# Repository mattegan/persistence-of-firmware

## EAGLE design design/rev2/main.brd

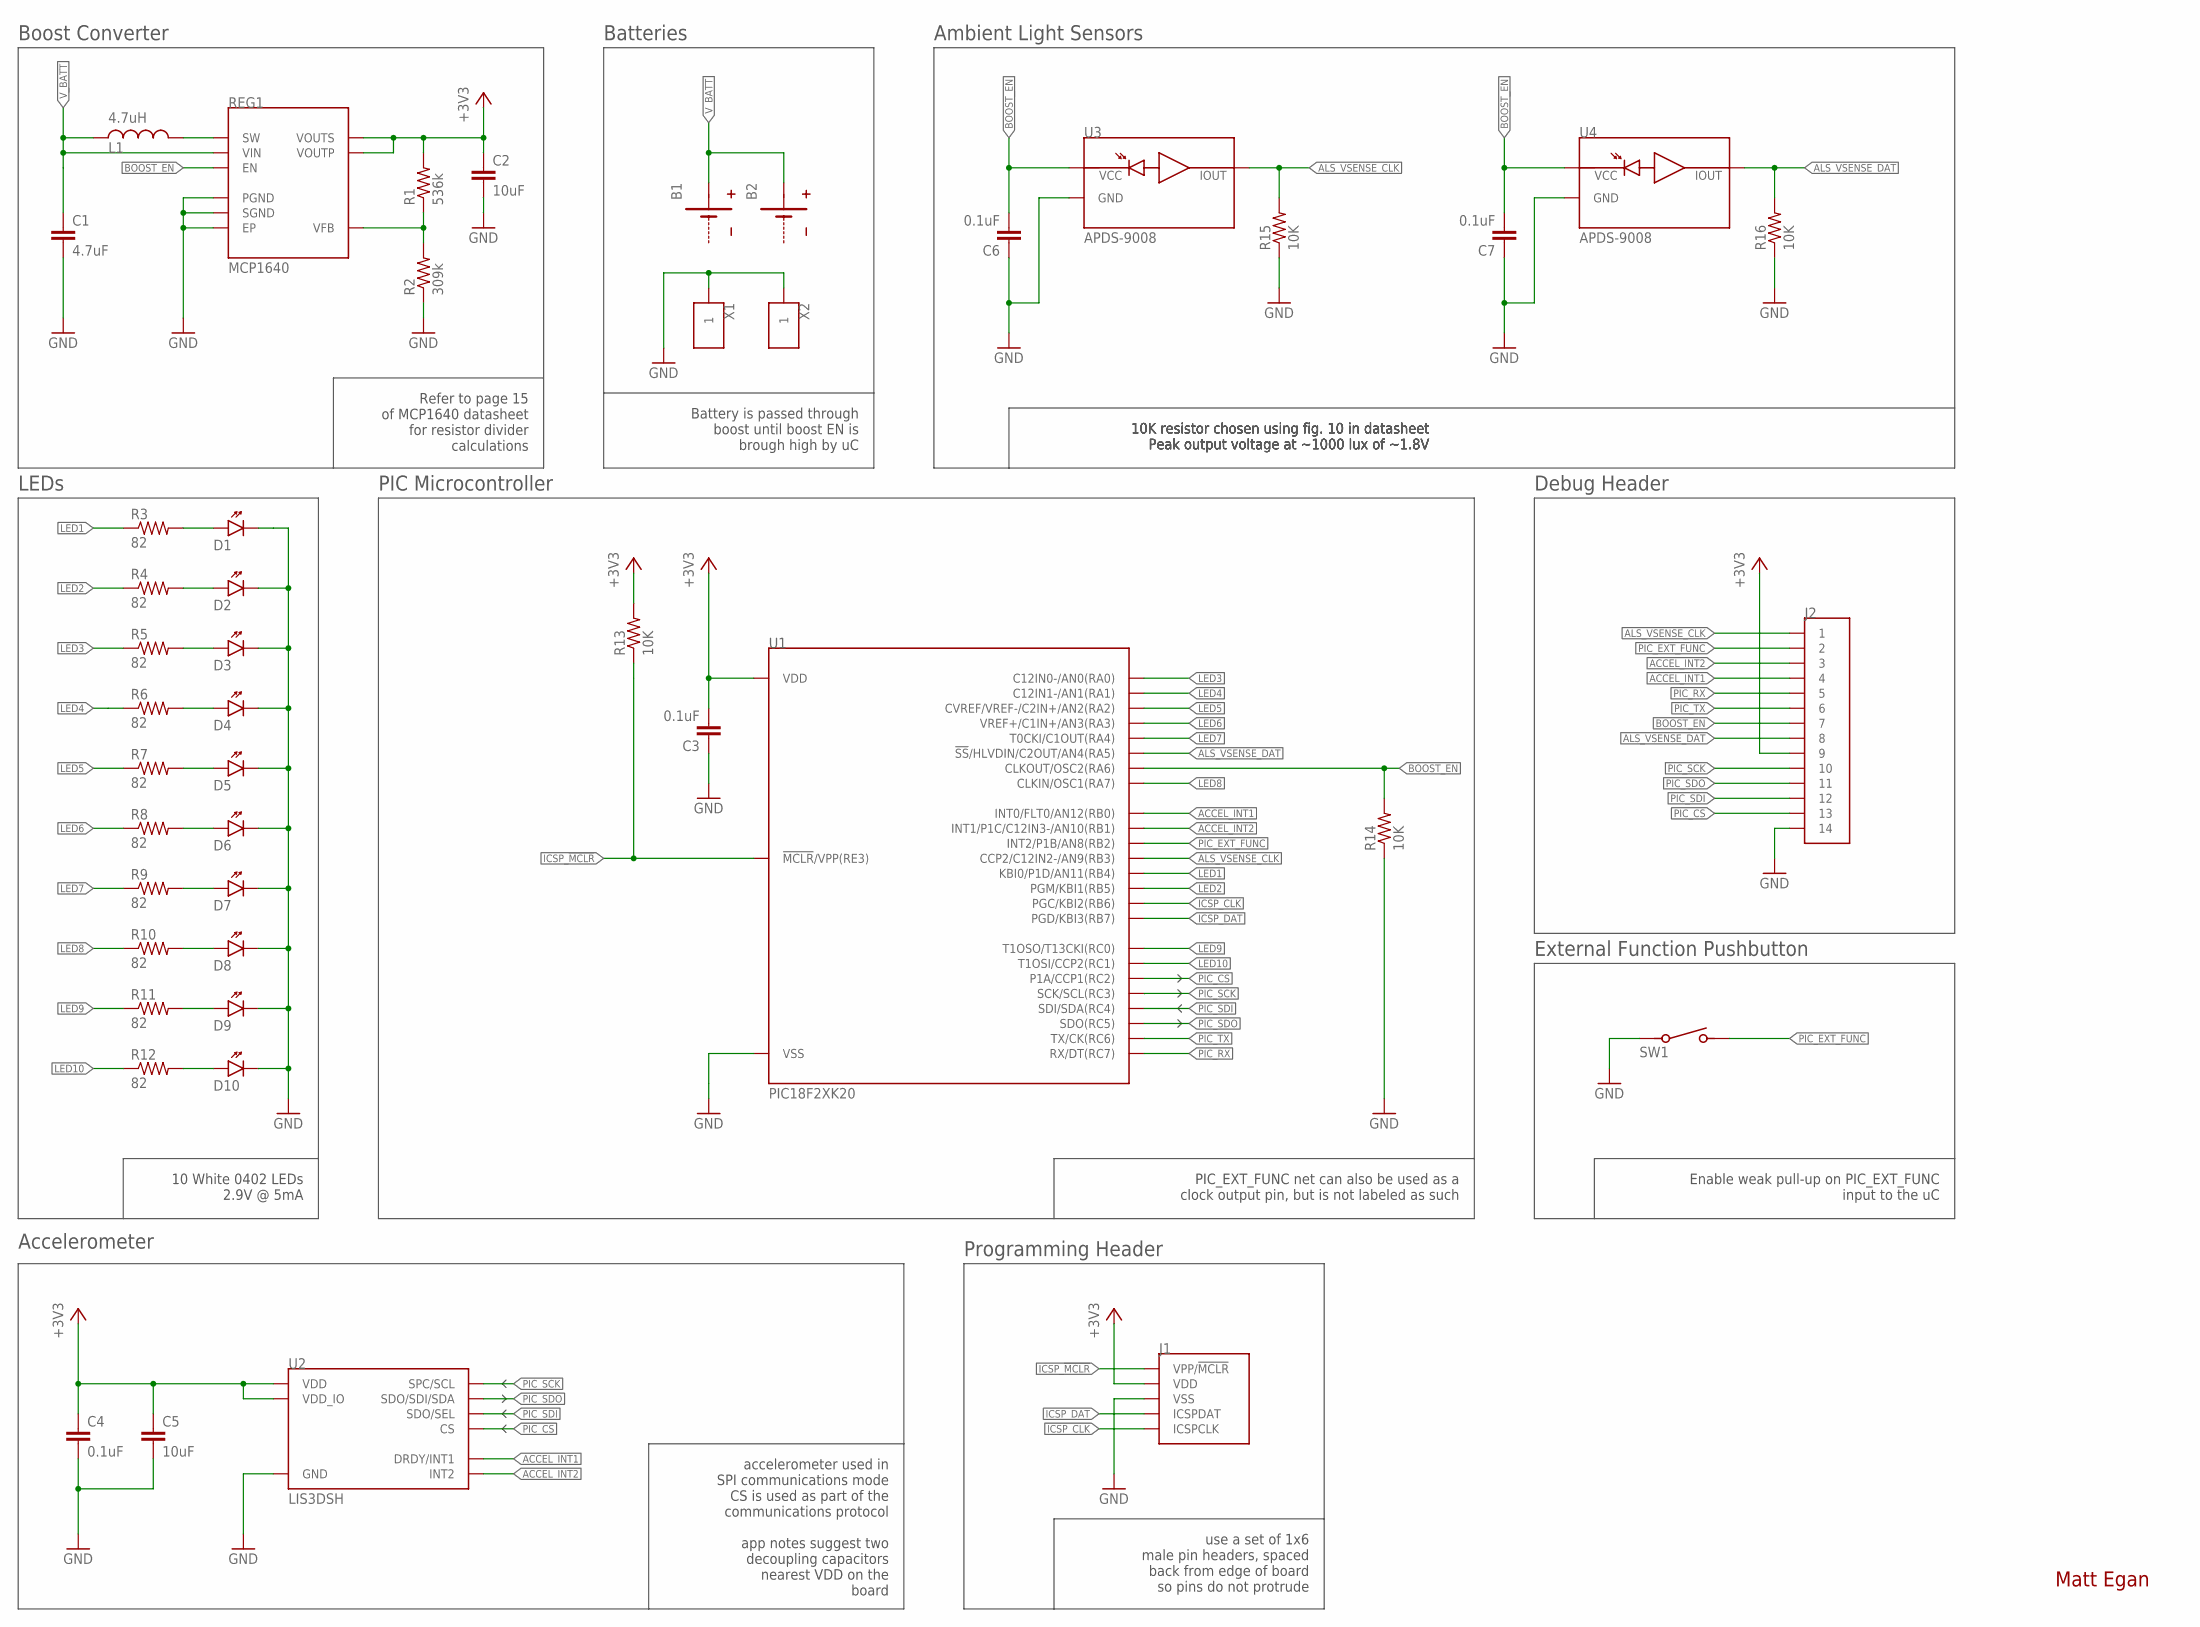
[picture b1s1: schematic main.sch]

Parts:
B1, B2: BATTERY-POS-HALF; CR20XX-PLATED
C1: 4.7uF; SMD-0603
C2: 10uF; SMD-0603
C3, C4, C6, C7: 0.1uF; SMD-0805
C5: 10uF; SMD-0805
D1, D2, D3, D4, D5, D6, D7, D8, D9, D10: LED0603; SMD-0603-P
J1: ICSP-HEADER1X6-0.1-ICSP-PADS; 1X6-0.1-ICSP-PADS
J2: HEADER-141X14-0.05-PADS; 1X14-0.05-PADS
L1: 4.7uH; VLF403210MT
R1: 536k; SMD-0603
R2: 309k; SMD-0603
R3, R4, R5, R6, R7, R8, R9, R10, R11, R12: 82; SMD-0603
R13, R14, R15, R16: 10K; SMD-0603
REG1: MCP1640; DFN-8(2X3)
SW1: B3U-3000P
U1: PIC18F2XK20; QFN-28
U2: LIS3DSH; LGA-16
U3, U4: APDS-9008; AVAGO-CHIPLED6
X1, X2: TE-2199248-X

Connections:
+3V3: C2.1, C3.2, C4.1, C5.1, J1.P$2 (VDD), J2.P$9 (9), R1.2, R13.2, REG1.6 (VOUTP), REG1.7 (VOUTS), U1.P$17 (VDD), U2.P$1 (VDD_IO), U2.P$14 (VDD), U2.P$15 (VDD)
ACCEL_INT1: J2.P$4 (4), U1.P$18 (INT0/FLT0/AN12(RB0)), U2.P$11 (DRDY/INT1)
ACCEL_INT2: J2.P$3 (3), U1.P$19 (INT1/P1C/C12IN3-/AN10(RB1)), U2.P$9 (INT2)
ALS_VSENSE_CLK: J2.P$1 (1), R15.2, U1.P$21 (CCP2/C12IN2-/AN9(RB3)), U3.P$6 (P$IOUT)
ALS_VSENSE_DAT: J2.P$8 (8), R16.2, U1.P$4 (!SS!/HLVDIN/C2OUT/AN4(RA5)), U4.P$6 (P$IOUT)
BOOST_EN: C6.2, C7.2, J2.P$7 (7), R14.2, REG1.4 (EN), U1.P$7 (CLKOUT/OSC2(RA6)), U3.P$1 (P$VCC), U4.P$1 (P$VCC)
GND: C1.2, C2.2, C3.1, C4.2, C5.2, C6.1, C7.1, D1.-, D2.-, D3.-, D4.-, D5.-, D6.-, D7.-, D8.-, D9.-, D10.-, J1.P$3 (VSS), J2.P$14 (14), R2.1, R14.1, R15.1, R16.1, REG1.2 (SGND), REG1.3 (PGND), REG1.EP, SW1.SW$1 (1), U1.P$5 (VSS), U1.P$16 (VSS), U2.P$5 (GND), U2.P$10 (GND), U2.P$12 (GND), U2.P$13 (GND), U2.P$16 (GND), U3.P$4 (GND), U4.P$4 (GND), X1.P$1, X1.P$2, X2.P$1, X2.P$2
ICSP_!MCLR!: J1.P$1 (VPP/!MCLR!), R13.1, U1.P$26 (!MCLR!/VPP(RE3))
ICSP_CLK: J1.P$5 (ICSPCLK), U1.P$24 (PGC/KBI2(RB6))
ICSP_DAT: J1.P$4 (ICSPDAT), U1.P$25 (PGD/KBI3(RB7))
LED1: R3.1, U1.P$22 (KBI0/P1D/AN11(RB4))
LED2: R4.1, U1.P$23 (PGM/KBI1(RB5))
LED3: R5.1, U1.P$27 (C12IN0-/AN0(RA0))
LED4: R6.1, U1.P$28 (C12IN1-/AN1(RA1))
LED5: R7.1, U1.P$1 (CVREF/VREF-/C2IN+/AN2(RA2))
LED6: R8.1, U1.P$2 (VREF+/C1IN+/AN3(RA3))
LED7: R9.1, U1.P$3 (T0CKI/C1OUT(RA4))
LED8: R10.1, U1.P$6 (CLKIN/OSC1(RA7))
LED9: R11.1, U1.P$8 (T1OSO/T13CKI(RC0))
LED10: R12.1, U1.P$9 (T1OSI/CCP2(RC1))
unnamed: L1.P$2 (2), REG1.5 (SW)
unnamed: R1.1, R2.2, REG1.1 (VFB)
unnamed: D1.+, R3.2
unnamed: D2.+, R4.2
unnamed: D3.+, R5.2
unnamed: D4.+, R6.2
unnamed: D5.+, R7.2
unnamed: D6.+, R8.2
unnamed: D7.+, R9.2
unnamed: D8.+, R10.2
unnamed: D9.+, R11.2
unnamed: D10.+, R12.2
PIC_CS: J2.P$13 (13), U1.P$10 (P1A/CCP1(RC2)), U2.P$8 (CS)
PIC_EXT_FUNC: J2.P$2 (2), SW1.SW$2 (3), U1.P$20 (INT2/P1B/AN8(RB2))
PIC_RX: J2.P$5 (5), U1.P$15 (RX/DT(RC7))
PIC_SCK: J2.P$10 (10), U1.P$11 (SCK/SCL(RC3)), U2.P$4 (SPC/SCL)
PIC_SDI: J2.P$12 (12), U1.P$12 (SDI/SDA(RC4)), U2.P$7 (SDO/SEL)
PIC_SDO: J2.P$11 (11), U1.P$13 (SDO(RC5)), U2.P$6 (SDO/SDI/SDA)
PIC_TX: J2.P$6 (6), U1.P$14 (TX/CK(RC6))
V_BATT: B1.P$1, B2.P$1, C1.1, L1.P$1 (1), REG1.8 (VIN)

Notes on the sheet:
Matt Egan
Accelerometer
Refer to page 15 of MCP1640 datasheet for resistor divider calculations
Boost Converter
Batteries
LEDs
10 White 0402 LEDs 2.9V @ 5mA
Programming Header
Ambient Light Sensors
10K resistor chosen using fig. 10 in datasheet Peak output voltage at ~1000 lux of ~1.8V
use a set of 1x6 male pin headers, spaced back from edge of board so pins do not protrude
Debug Header
PIC Microcontroller
accelerometer used in SPI communications mode CS is used as part of the communications protocol app notes suggest two decoupling capacitors nearest VDD on the board
External Function Pushbutton
PIC_EXT_FUNC net can also be used as a clock output pin, but is not labeled as such
Battery is passed through boost until boost EN is brough high by uC
Enable weak pull-up on PIC_EXT_FUNC input to the uC

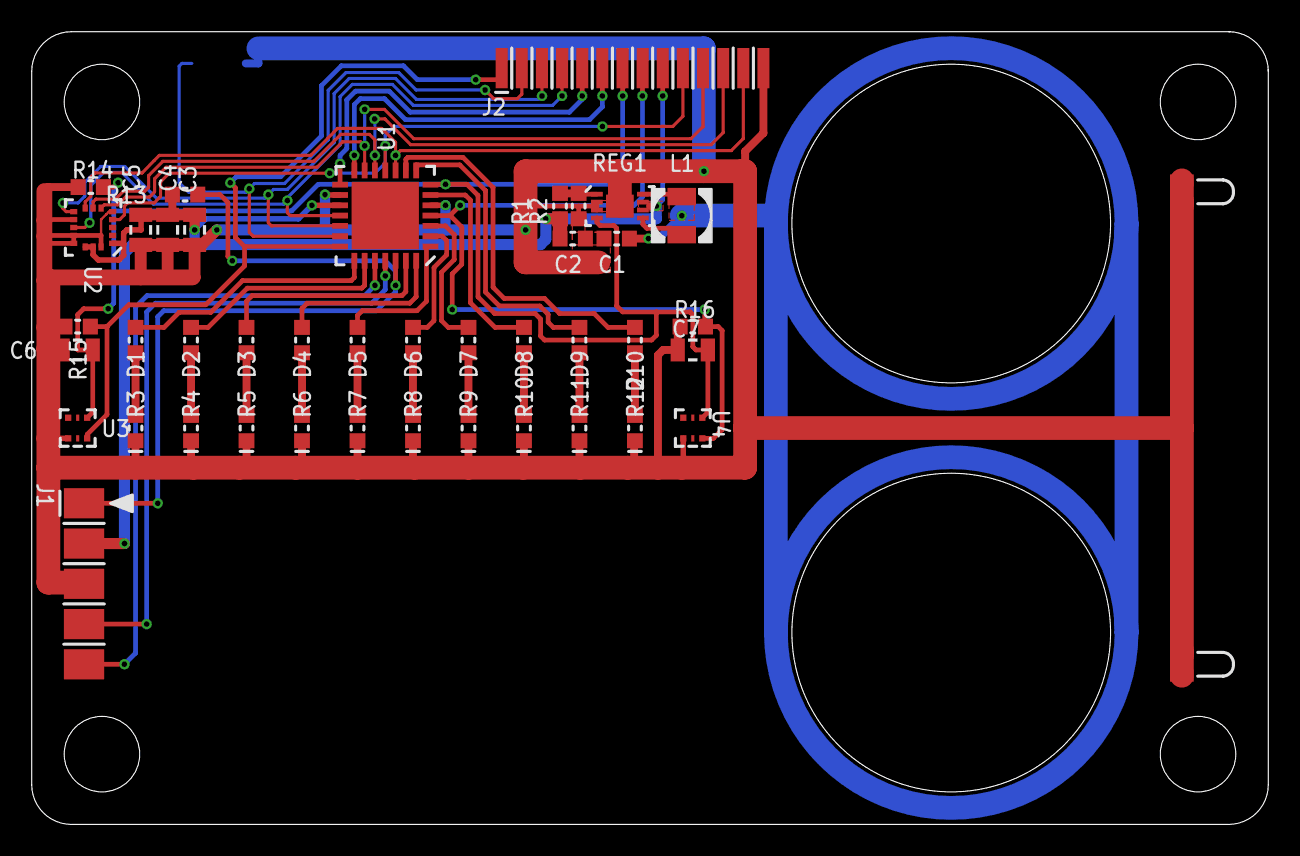
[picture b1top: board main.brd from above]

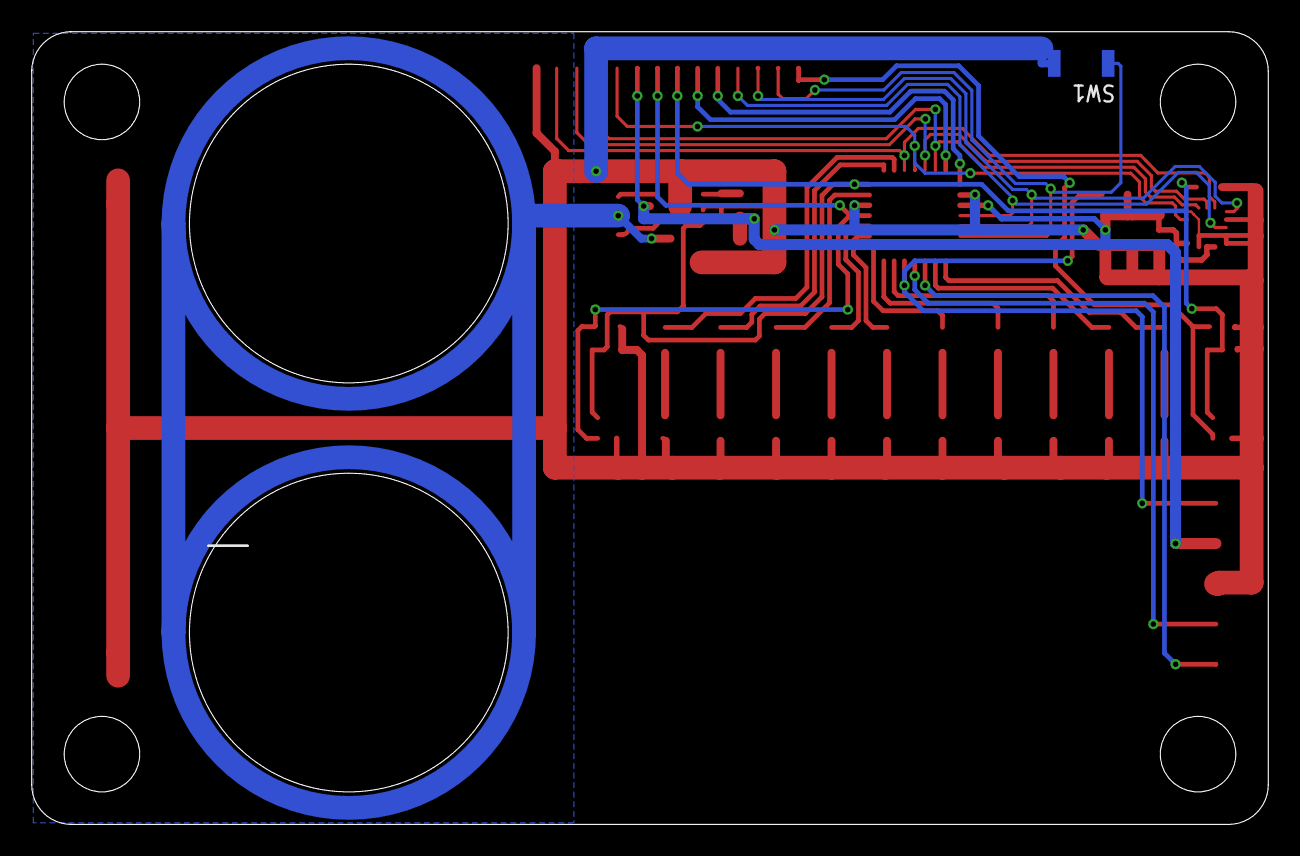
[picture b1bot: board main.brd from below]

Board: 2 copper layers, 78.0 x 50.0 mm, 46 parts (3 on the bottom side), 40 nets.

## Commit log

2015-07-18 Initial Commit
    rev0 board completed, MPLAB X project initialized
2015-07-18 [CNG] moved readme
    readme was in the wrong directory
2015-08-02 [CNG] - implemented basic functionality
    - SPI working, communicating with Accelerometer
    - UART working to communicate with a USB-UART bridge
    - implements peak detection, the LEDs (should) come on at the edge of
    each shake direction
2015-08-02 [ADD] - created an png image decoder
    - simple node.js library using get-pixels to take a black and white png
    and turn it into a string I can copy into my C code
2015-08-02 [CNG] - displays image (crudely) in midair
    - now displaying image buffer in midair, with room for improvement
2015-08-02 [CNG] - update comments, fix tabs
2015-09-05 [CNG] - duplicated designs to rev1 folder, implemented updates, initial rev1 layout
2016-05-26 [CNG] - more schematic and layout progress on rev1
2016-05-27 [CNG] - finished most of the new electrical changes for rev1 (see planning.txt), starting layout
2016-06-15 [add] - rev2, mechanical drawings of PCB and supporting elements
    Copied rev1 as rev2 to make significant changes, still may go with rev1
    design changes. Started mocking up all elements of the card in
    solidworks as it's getting more complicated.
2016-06-29 [CNG] - finished most routing on rev2, added new mechanical drawings (not up to date with POR)
